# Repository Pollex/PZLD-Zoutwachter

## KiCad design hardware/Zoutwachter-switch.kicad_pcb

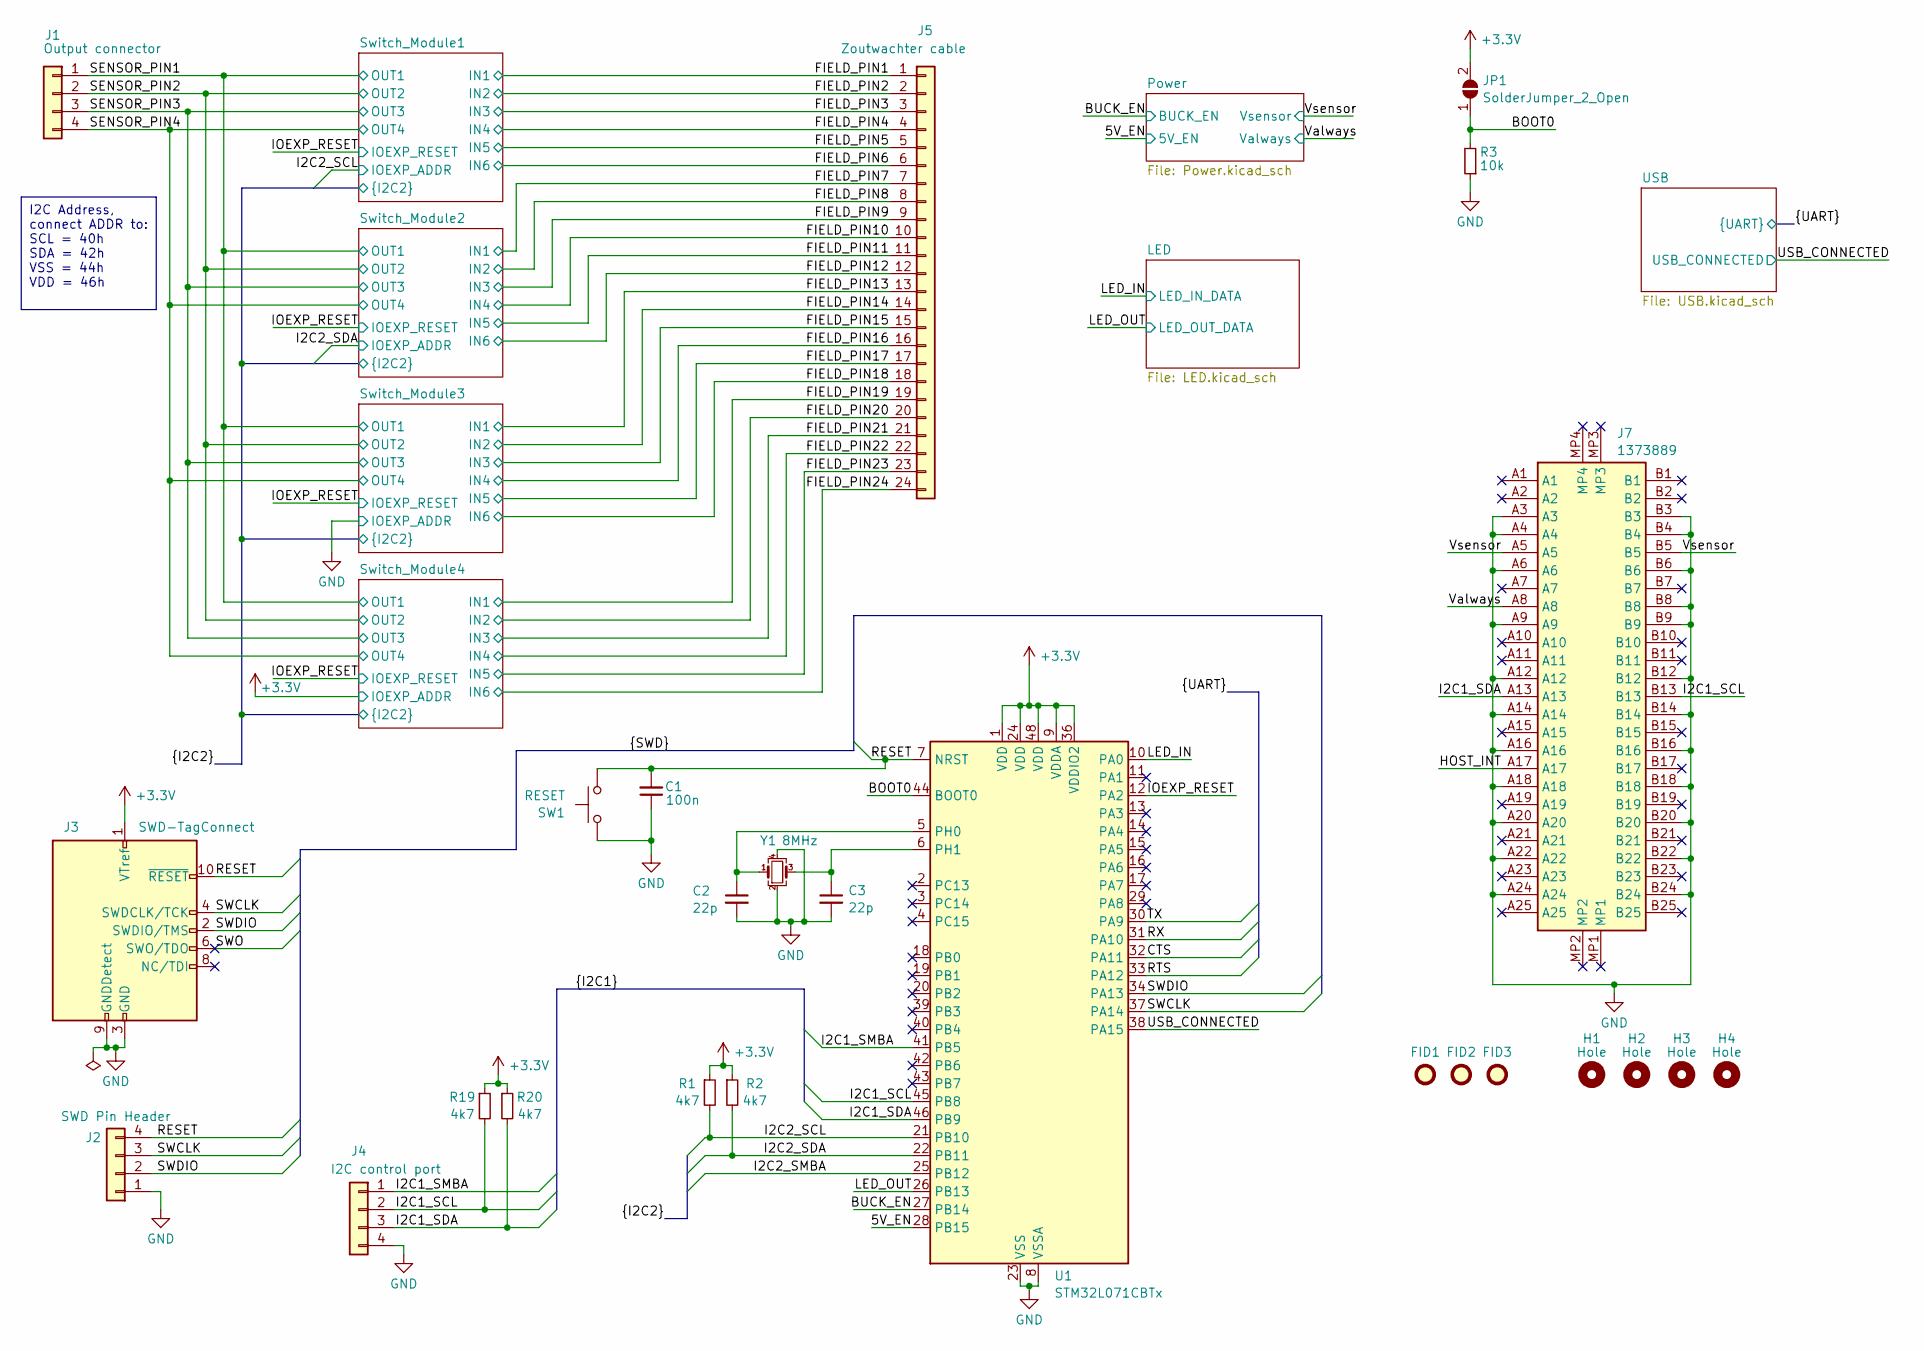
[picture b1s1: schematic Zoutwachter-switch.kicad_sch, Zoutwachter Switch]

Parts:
C1: 100n; C_0603_1608Metric; LCSC MFR YAGEO
C2, C3: 22p; C_0603_1608Metric; LCSC MFR Samsung Electro-Mechanics
FID1, FID2, FID3: Fiducial; Fiducial_1mm_Mask2mm
H1, H2, H3, H4: Hole; MountingHole_3.2mm_M3
J1: Output connector; 1755752
J2: SWD Pin Header; DEALON DW254S-22-04-85 SMD 2x2pin 2.54mm straight; LCSC MFR DEALON
J3: SWD-TagConnect; Tag-Connect_TC2050-IDC-NL_2x05_P1.27mm_Vertical_with_bottom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
J4: I2C control port; DEALON DW254S-22-04-85 SMD 2x2pin 2.54mm straight; LCSC MFR DEALON
J5: Zoutwachter cable; 1755956
J7: 1373889; Manufacturer_Part_Number 1373889
JP1: SolderJumper_2_Open; SolderJumper-2_P1.3mm_Open_RoundedPad1.0x1.5mm
R1, R2, R19, R20: 4k7; R_0603_1608Metric; LCSC MFR UNI-ROYAL(Uniroyal Elec)
R3: 10k; R_0603_1608Metric; LCSC MFR UNI-ROYAL(Uniroyal Elec)
SW1: RESET; SW_Push_1P1T_XKB_TS-1187A; LCSC MFR XKB Connectivity
U1: STM32L071CBTx; LQFP-48_7x7mm_P0.5mm; LCSC MFR STMicroelectronics
Y1: 8MHz; Crystal_SMD_3225-4Pin_3.2x2.5mm; LCSC MFR ECS INTERNATIONAL INC

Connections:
/5V_EN: U1.28 (PB15); also elsewhere on the board
/BOOT0: JP1.1 (A), R3.2, U1.44 (BOOT0)
/BUCK_EN: U1.27 (PB14); also elsewhere on the board
/CTS: U1.32 (PA11); also elsewhere on the board
/FIELD_PIN1: J5.1; also elsewhere on the board
/FIELD_PIN2: J5.2; also elsewhere on the board
/FIELD_PIN3: J5.3; also elsewhere on the board
/FIELD_PIN4: J5.4; also elsewhere on the board
/FIELD_PIN5: J5.5; also elsewhere on the board
/FIELD_PIN6: J5.6; also elsewhere on the board
/FIELD_PIN7: J5.7; also elsewhere on the board
/FIELD_PIN8: J5.8; also elsewhere on the board
/FIELD_PIN9: J5.9; also elsewhere on the board
/FIELD_PIN10: J5.10; also elsewhere on the board
/FIELD_PIN11: J5.11; also elsewhere on the board
/FIELD_PIN12: J5.12; also elsewhere on the board
/FIELD_PIN13: J5.13; also elsewhere on the board
/FIELD_PIN14: J5.14; also elsewhere on the board
/FIELD_PIN15: J5.15; also elsewhere on the board
/FIELD_PIN16: J5.16; also elsewhere on the board
/FIELD_PIN17: J5.17; also elsewhere on the board
/FIELD_PIN18: J5.18; also elsewhere on the board
/FIELD_PIN19: J5.19; also elsewhere on the board
/FIELD_PIN20: J5.20; also elsewhere on the board
/FIELD_PIN21: J5.21; also elsewhere on the board
/FIELD_PIN22: J5.22; also elsewhere on the board
/FIELD_PIN23: J5.23; also elsewhere on the board
/FIELD_PIN24: J5.24; also elsewhere on the board
/HOST_INT: J7.A17
/I2C1_SCL: J4.2, J7.B13, R19.2, U1.45 (PB8)
/I2C1_SDA: J4.3, J7.A13, R20.2, U1.46 (PB9)
/I2C1_SMBA: J4.1, U1.41 (PB5)
/I2C2_SCL: R1.2, U1.21 (PB10); also elsewhere on the board
/I2C2_SDA: R2.2, U1.22 (PB11); also elsewhere on the board
/I2C2_SMBA: U1.25 (PB12)
/IOEXP_RESET: U1.12 (PA2); also elsewhere on the board
/LED_IN: U1.10 (PA0); also elsewhere on the board
/LED_OUT: U1.26 (PB13); also elsewhere on the board
/RESET: C1.2, J2.4, J3.10 (~RESET), SW1.2, U1.7 (NRST)
/RTS: U1.33 (PA12); also elsewhere on the board
/RX: U1.31 (PA10); also elsewhere on the board
/SENSOR_PIN1: J1.1; also elsewhere on the board
/SENSOR_PIN2: J1.2; also elsewhere on the board
/SENSOR_PIN3: J1.3; also elsewhere on the board
/SENSOR_PIN4: J1.4; also elsewhere on the board
/SWCLK: J2.3, J3.4 (SWDCLK/TCK), U1.37 (PA14)
/SWDIO: J2.2, J3.2 (SWDIO/TMS), U1.34 (PA13)
/SWO: J3.6 (SWO/TDO)
/TX: U1.30 (PA9); also elsewhere on the board
/USB_CONNECTED: U1.38 (PA15); also elsewhere on the board
/Valways: J7.A8; also elsewhere on the board
/Vsensor: J7.A5, J7.B5; also elsewhere on the board
GND: C1.1, C2.2, C3.2, J2.1, J3.3 (GND), J3.5 (GND), J3.9 (GNDDetect), J4.4, J7.A3, J7.A4, J7.A6, J7.A9, J7.A12, J7.A14, J7.A16, J7.A18, J7.A20, J7.A22, J7.A24, J7.B3, J7.B4, J7.B6, J7.B8, J7.B9, J7.B12, J7.B14, J7.B16, J7.B18, J7.B20, J7.B22, J7.B24, R3.1, SW1.1, U1.8 (VSSA), U1.23 (VSS), U1.35 (VSS), U1.47 (VSS), Y1.2, Y1.4; also elsewhere on the board
unnamed: C2.1, U1.5 (PH0), Y1.1
unnamed: C3.1, U1.6 (PH1), Y1.3

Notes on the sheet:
I2C Address, connect ADDR to: ﻿SCL = 40h SDA = 42h VSS = 44h VDD = 46h

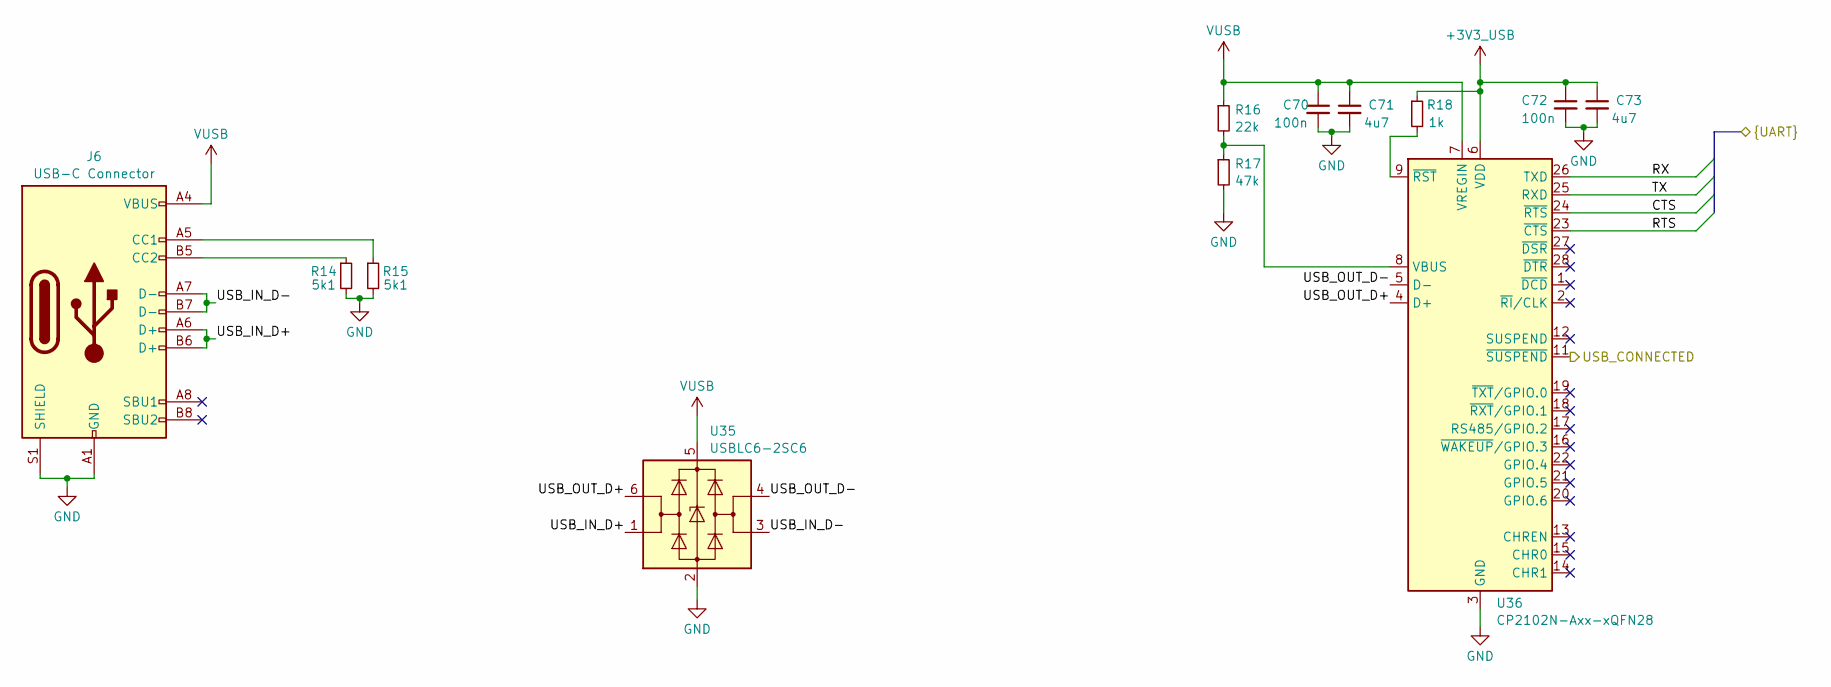
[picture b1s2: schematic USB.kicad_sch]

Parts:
C70, C72: 100n; C_0603_1608Metric; LCSC MFR YAGEO
C71, C73: 4u7; C_0603_1608Metric; LCSC MFR Samsung Electro-Mechanics
J6: USB-C Connector; MOLEX_2171820001; LCSC MFR MOLEX
R14, R15: 5k1; R_0603_1608Metric; LCSC MFR UNI-ROYAL(Uniroyal Elec)
R16: 22k; R_0603_1608Metric; LCSC MFR UNI-ROYAL(Uniroyal Elec)
R17: 47k; R_0603_1608Metric; LCSC MFR UNI-ROYAL(Uniroyal Elec)
R18: 1k; R_0603_1608Metric; LCSC MFR UNI-ROYAL(Uniroyal Elec)
U35: USBLC6-2SC6; SOT-23-6; LCSC MFR STMicroelectronics
U36: CP2102N-Axx-xQFN28; QFN-28-1EP_5x5mm_P0.5mm_EP3.35x3.35mm; LCSC MFR SILICON LABS

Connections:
+3V3_USB: C72.1, C73.1, R18.1, U36.6 (VDD)
/CTS: U36.24 (~RTS); also elsewhere on the board
/RTS: U36.23 (~CTS); also elsewhere on the board
/RX: U36.26 (TXD); also elsewhere on the board
/TX: U36.25 (RXD); also elsewhere on the board
/USB/USB_IN_D+: J6.A6 (D+), J6.B6 (D+), U35.1 (I/O1)
/USB/USB_IN_D-: J6.A7 (D-), J6.B7 (D-), U35.3 (I/O2)
/USB/USB_OUT_D+: U35.6 (I/O1), U36.4 (D+)
/USB/USB_OUT_D-: U35.4 (I/O2), U36.5 (D-)
/USB_CONNECTED: U36.11 (~SUSPEND); also elsewhere on the board
GND: C70.2, C71.2, C72.2, C73.2, J6.A1 (GND), J6.A12 (GND), J6.B1 (GND), J6.B12 (GND), J6.S1 (SHIELD), R14.2, R15.2, R17.2, U35.2 (GND), U36.3 (GND), U36.29 (GND); also elsewhere on the board
unnamed: J6.A5 (CC1), R15.1
unnamed: J6.B5 (CC2), R14.1
unnamed: R16.2, R17.1, U36.8 (VBUS)
unnamed: R18.2, U36.9 (~RST)
VUSB: C70.1, C71.1, J6.A4 (VBUS), J6.A9 (VBUS), J6.B4 (VBUS), J6.B9 (VBUS), R16.1, U35.5 (VBUS), U36.7 (VREGIN); also elsewhere on the board

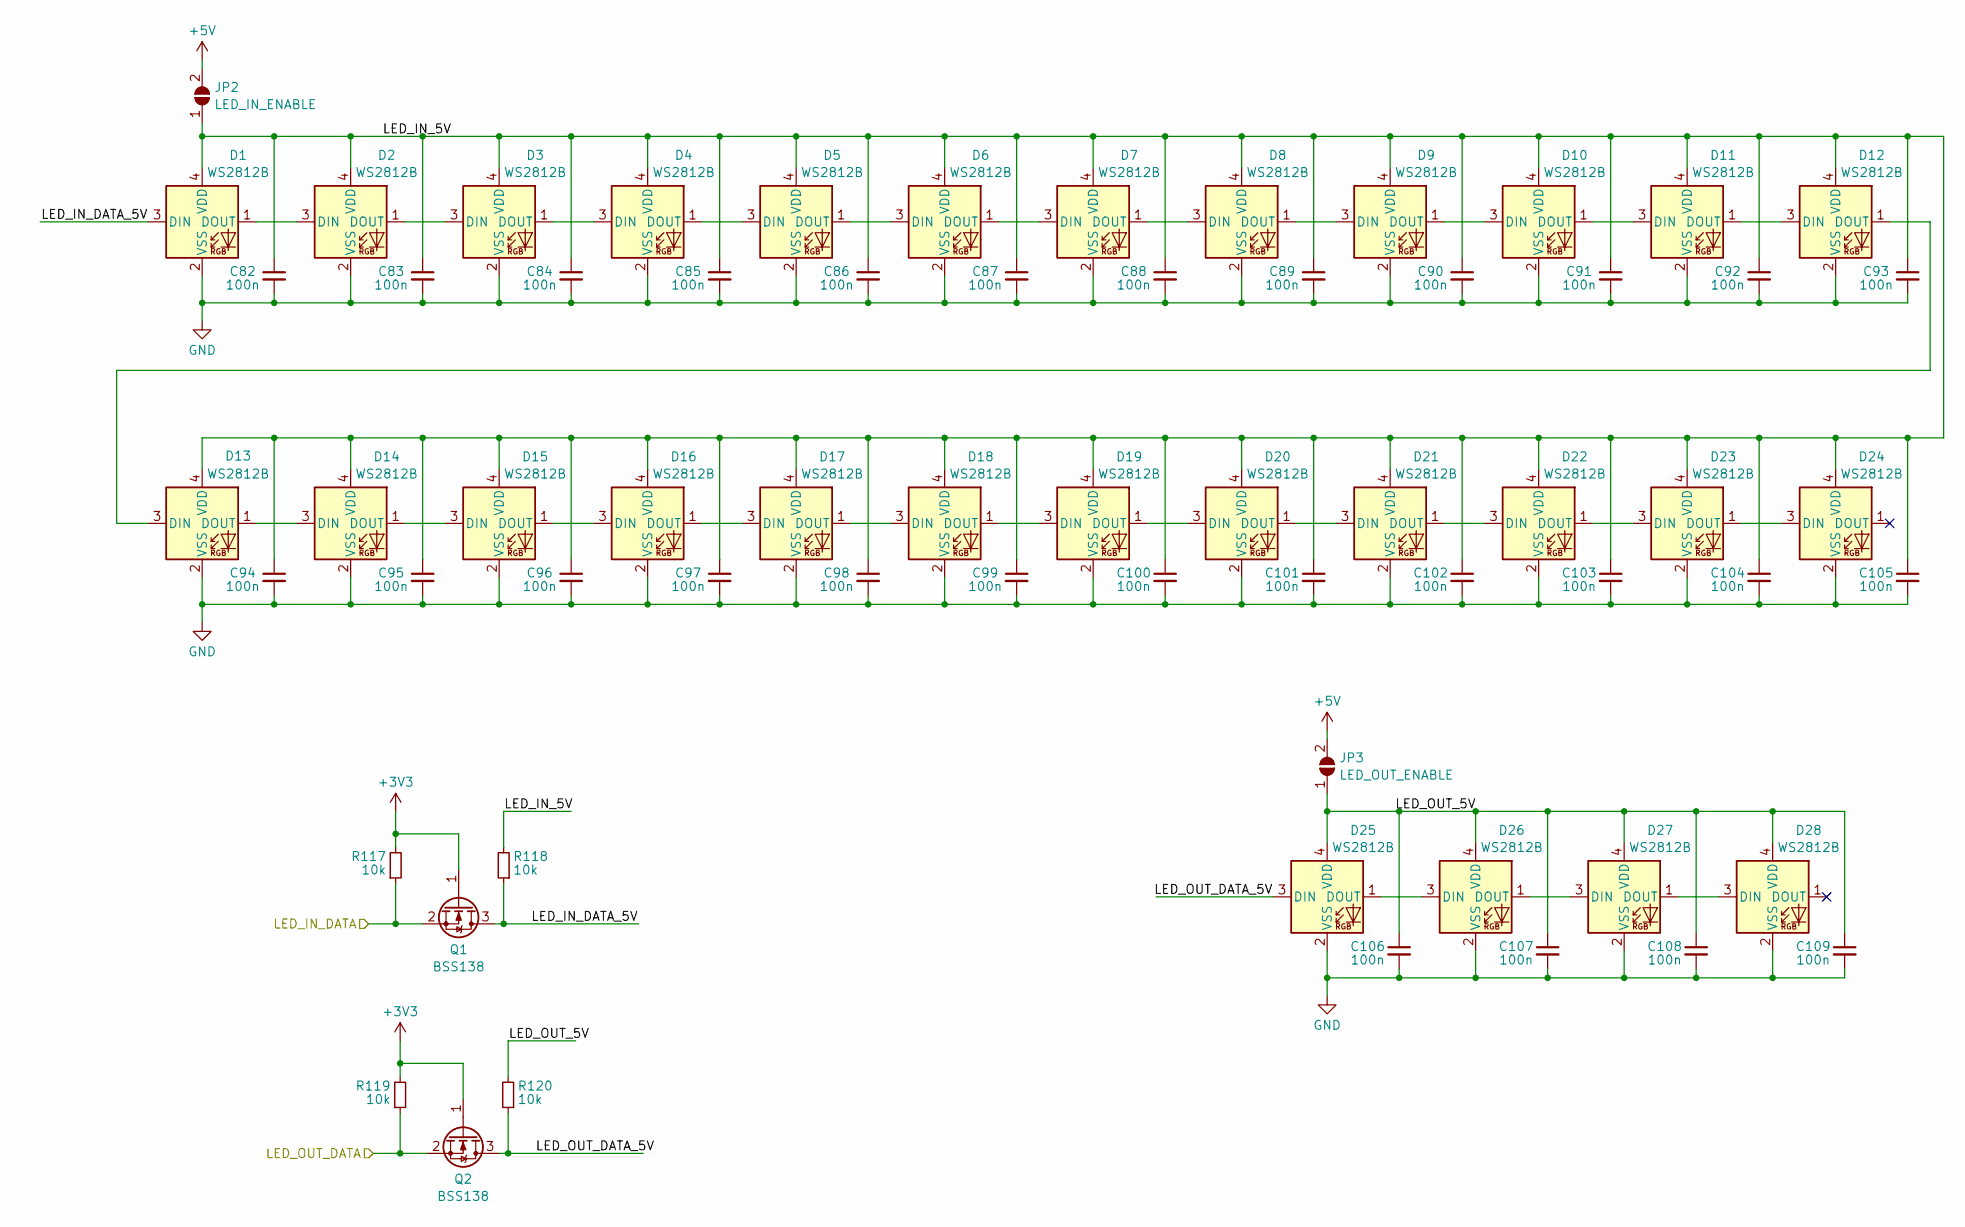
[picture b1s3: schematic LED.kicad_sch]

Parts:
C82, C83, C84, C85, C86, C87, C88, C89, C90, C91, C92, C93, C94, C95, C96, C97, C98, C99, C100, C101, C102, C103, C104, C105, C106, C107, C108, C109: 100n; C_0603_1608Metric; LCSC MFR YAGEO
D1, D2, D3, D4, D5, D6, D7, D8, D9, D10, D11, D12, D13, D14, D15, D16, D17, D18, D19, D20, D21, D22, D23, D24, D25, D26, D27, D28: WS2812B; WS2812B-2020; LCSC MFR Worldsemi
JP2: LED_IN_ENABLE; SolderJumper-2_P1.3mm_Open_RoundedPad1.0x1.5mm
JP3: LED_OUT_ENABLE; SolderJumper-2_P1.3mm_Open_RoundedPad1.0x1.5mm
Q1, Q2: BSS138; SOT-23
R117, R118, R119, R120: 10k; R_0603_1608Metric; LCSC MFR UNI-ROYAL(Uniroyal Elec)

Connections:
+5V: JP2.2 (B), JP3.2 (B); also elsewhere on the board
/LED/LED_IN_5V: C82.1, C83.1, C84.1, C85.1, C86.1, C87.1, C88.1, C89.1, C90.1, C91.1, C92.1, C93.1, C94.1, C95.1, C96.1, C97.1, C98.1, C99.1, C100.1, C101.1, C102.1, C103.1, C104.1, C105.1, D1.4 (VDD), D2.4 (VDD), D3.4 (VDD), D4.4 (VDD), D5.4 (VDD), D6.4 (VDD), D7.4 (VDD), D8.4 (VDD), D9.4 (VDD), D10.4 (VDD), D11.4 (VDD), D12.4 (VDD), D13.4 (VDD), D14.4 (VDD), D15.4 (VDD), D16.4 (VDD), D17.4 (VDD), D18.4 (VDD), D19.4 (VDD), D20.4 (VDD), D21.4 (VDD), D22.4 (VDD), D23.4 (VDD), D24.4 (VDD), JP2.1 (A), R118.2
/LED/LED_IN_DATA_5V: D1.3 (DIN), Q1.3 (D), R118.1
/LED/LED_OUT_5V: C106.1, C107.1, C108.1, C109.1, D25.4 (VDD), D26.4 (VDD), D27.4 (VDD), D28.4 (VDD), JP3.1 (A), R120.2
/LED/LED_OUT_DATA_5V: D25.3 (DIN), Q2.3 (D), R120.1
/LED_IN: Q1.2 (S), R117.1; also elsewhere on the board
/LED_OUT: Q2.2 (S), R119.1; also elsewhere on the board
GND: C82.2, C83.2, C84.2, C85.2, C86.2, C87.2, C88.2, C89.2, C90.2, C91.2, C92.2, C93.2, C94.2, C95.2, C96.2, C97.2, C98.2, C99.2, C100.2, C101.2, C102.2, C103.2, C104.2, C105.2, C106.2, C107.2, C108.2, C109.2, D1.2 (VSS), D2.2 (VSS), D3.2 (VSS), D4.2 (VSS), D5.2 (VSS), D6.2 (VSS), D7.2 (VSS), D8.2 (VSS), D9.2 (VSS), D10.2 (VSS), D11.2 (VSS), D12.2 (VSS), D13.2 (VSS), D14.2 (VSS), D15.2 (VSS), D16.2 (VSS), D17.2 (VSS), D18.2 (VSS), D19.2 (VSS), D20.2 (VSS), D21.2 (VSS), D22.2 (VSS), D23.2 (VSS), D24.2 (VSS), D25.2 (VSS), D26.2 (VSS), D27.2 (VSS), D28.2 (VSS); also elsewhere on the board
unnamed: D1.1 (DOUT), D2.3 (DIN)
unnamed: D2.1 (DOUT), D3.3 (DIN)
unnamed: D3.1 (DOUT), D4.3 (DIN)
unnamed: D4.1 (DOUT), D5.3 (DIN)
unnamed: D5.1 (DOUT), D6.3 (DIN)
unnamed: D6.1 (DOUT), D7.3 (DIN)
unnamed: D7.1 (DOUT), D8.3 (DIN)
unnamed: D8.1 (DOUT), D9.3 (DIN)
unnamed: D9.1 (DOUT), D10.3 (DIN)
unnamed: D10.1 (DOUT), D11.3 (DIN)
unnamed: D11.1 (DOUT), D12.3 (DIN)
unnamed: D12.1 (DOUT), D13.3 (DIN)
unnamed: D13.1 (DOUT), D14.3 (DIN)
unnamed: D14.1 (DOUT), D15.3 (DIN)
unnamed: D15.1 (DOUT), D16.3 (DIN)
unnamed: D16.1 (DOUT), D17.3 (DIN)
unnamed: D17.1 (DOUT), D18.3 (DIN)
unnamed: D18.1 (DOUT), D19.3 (DIN)
unnamed: D19.1 (DOUT), D20.3 (DIN)
unnamed: D20.1 (DOUT), D21.3 (DIN)
unnamed: D21.1 (DOUT), D22.3 (DIN)
unnamed: D22.1 (DOUT), D23.3 (DIN)
unnamed: D23.1 (DOUT), D24.3 (DIN)
unnamed: D25.1 (DOUT), D26.3 (DIN)
unnamed: D26.1 (DOUT), D27.3 (DIN)
unnamed: D27.1 (DOUT), D28.3 (DIN)

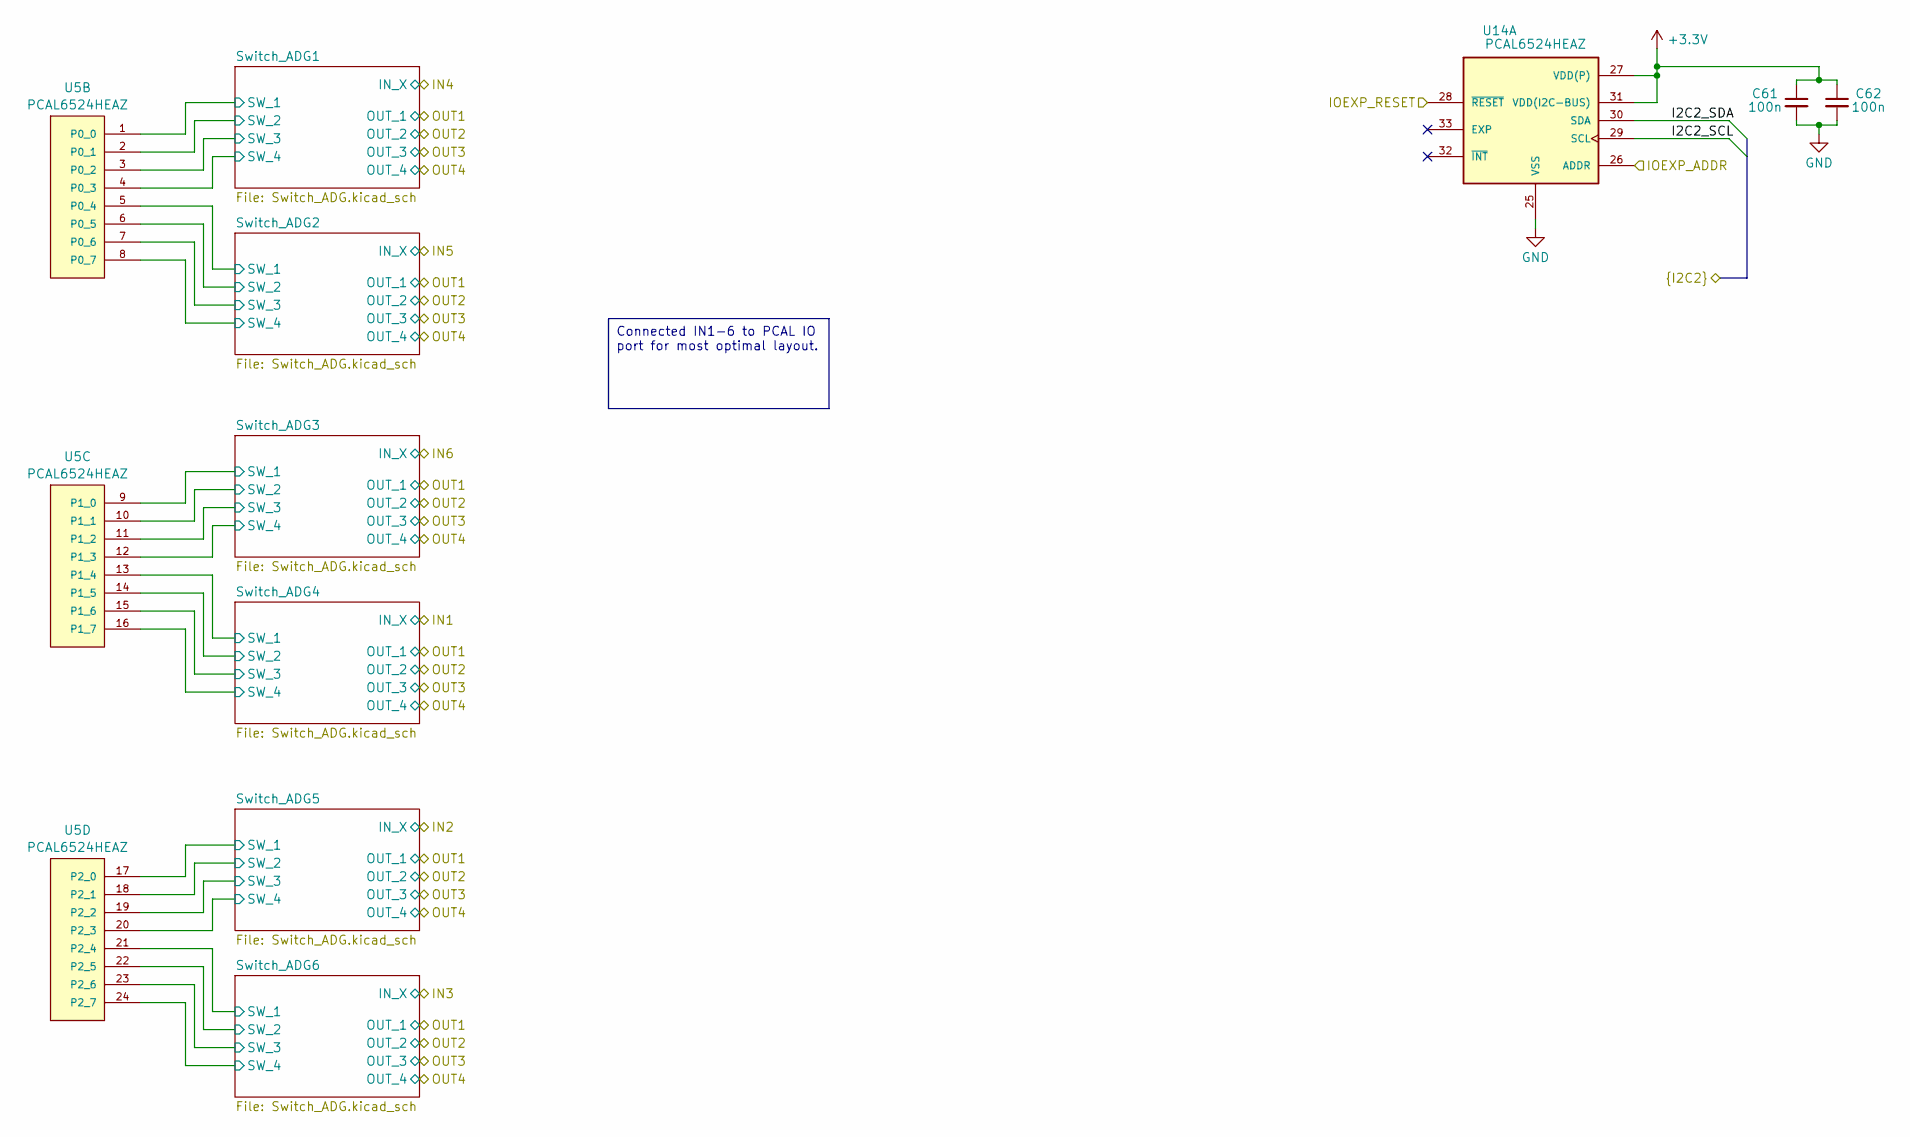
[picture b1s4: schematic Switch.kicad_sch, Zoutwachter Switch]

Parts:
C61, C62: 100n; C_0603_1608Metric; LCSC MFR YAGEO
U5, U14: PCAL6524HEAZ; LCSC Part # C3000497

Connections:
/I2C2_SCL: U5.26 (ADDR), U5.29 (SCL), U14.29 (SCL); also elsewhere on the board
/I2C2_SDA: U5.30 (SDA), U14.30 (SDA); also elsewhere on the board
/IOEXP_RESET: U5.28 (~RESET), U14.28 (~RESET); also elsewhere on the board
/Switch_Module1/Switch_ADG1/SW_1: U5.1 (P0_0); also elsewhere on the board
/Switch_Module1/Switch_ADG1/SW_2: U5.2 (P0_1); also elsewhere on the board
/Switch_Module1/Switch_ADG1/SW_3: U5.3 (P0_2); also elsewhere on the board
/Switch_Module1/Switch_ADG1/SW_4: U5.4 (P0_3); also elsewhere on the board
/Switch_Module1/Switch_ADG2/SW_1: U5.5 (P0_4); also elsewhere on the board
/Switch_Module1/Switch_ADG2/SW_2: U5.6 (P0_5); also elsewhere on the board
/Switch_Module1/Switch_ADG2/SW_3: U5.7 (P0_6); also elsewhere on the board
/Switch_Module1/Switch_ADG2/SW_4: U5.8 (P0_7); also elsewhere on the board
/Switch_Module1/Switch_ADG3/SW_1: U5.9 (P1_0); also elsewhere on the board
/Switch_Module1/Switch_ADG3/SW_2: U5.10 (P1_1); also elsewhere on the board
/Switch_Module1/Switch_ADG3/SW_3: U5.11 (P1_2); also elsewhere on the board
/Switch_Module1/Switch_ADG3/SW_4: U5.12 (P1_3); also elsewhere on the board
/Switch_Module1/Switch_ADG4/SW_1: U5.13 (P1_4); also elsewhere on the board
/Switch_Module1/Switch_ADG4/SW_2: U5.14 (P1_5); also elsewhere on the board
/Switch_Module1/Switch_ADG4/SW_3: U5.15 (P1_6); also elsewhere on the board
/Switch_Module1/Switch_ADG4/SW_4: U5.16 (P1_7); also elsewhere on the board
/Switch_Module1/Switch_ADG5/SW_1: U5.17 (P2_0); also elsewhere on the board
/Switch_Module1/Switch_ADG5/SW_2: U5.18 (P2_1); also elsewhere on the board
/Switch_Module1/Switch_ADG5/SW_3: U5.19 (P2_2); also elsewhere on the board
/Switch_Module1/Switch_ADG5/SW_4: U5.20 (P2_3); also elsewhere on the board
/Switch_Module1/Switch_ADG6/SW_1: U5.21 (P2_4); also elsewhere on the board
/Switch_Module1/Switch_ADG6/SW_2: U5.22 (P2_5); also elsewhere on the board
/Switch_Module1/Switch_ADG6/SW_3: U5.23 (P2_6); also elsewhere on the board
/Switch_Module1/Switch_ADG6/SW_4: U5.24 (P2_7); also elsewhere on the board
/Switch_Module4/Switch_ADG1/SW_1: U14.1 (P0_0); also elsewhere on the board
/Switch_Module4/Switch_ADG1/SW_2: U14.2 (P0_1); also elsewhere on the board
/Switch_Module4/Switch_ADG1/SW_3: U14.3 (P0_2); also elsewhere on the board
/Switch_Module4/Switch_ADG1/SW_4: U14.4 (P0_3); also elsewhere on the board
/Switch_Module4/Switch_ADG2/SW_1: U14.5 (P0_4); also elsewhere on the board
/Switch_Module4/Switch_ADG2/SW_2: U14.6 (P0_5); also elsewhere on the board
/Switch_Module4/Switch_ADG2/SW_3: U14.7 (P0_6); also elsewhere on the board
/Switch_Module4/Switch_ADG2/SW_4: U14.8 (P0_7); also elsewhere on the board
/Switch_Module4/Switch_ADG3/SW_1: U14.9 (P1_0); also elsewhere on the board
/Switch_Module4/Switch_ADG3/SW_2: U14.10 (P1_1); also elsewhere on the board
/Switch_Module4/Switch_ADG3/SW_3: U14.11 (P1_2); also elsewhere on the board
/Switch_Module4/Switch_ADG3/SW_4: U14.12 (P1_3); also elsewhere on the board
/Switch_Module4/Switch_ADG4/SW_1: U14.13 (P1_4); also elsewhere on the board
/Switch_Module4/Switch_ADG4/SW_2: U14.14 (P1_5); also elsewhere on the board
/Switch_Module4/Switch_ADG4/SW_3: U14.15 (P1_6); also elsewhere on the board
/Switch_Module4/Switch_ADG4/SW_4: U14.16 (P1_7); also elsewhere on the board
/Switch_Module4/Switch_ADG5/SW_1: U14.17 (P2_0); also elsewhere on the board
/Switch_Module4/Switch_ADG5/SW_2: U14.18 (P2_1); also elsewhere on the board
/Switch_Module4/Switch_ADG5/SW_3: U14.19 (P2_2); also elsewhere on the board
/Switch_Module4/Switch_ADG5/SW_4: U14.20 (P2_3); also elsewhere on the board
/Switch_Module4/Switch_ADG6/SW_1: U14.21 (P2_4); also elsewhere on the board
/Switch_Module4/Switch_ADG6/SW_2: U14.22 (P2_5); also elsewhere on the board
/Switch_Module4/Switch_ADG6/SW_3: U14.23 (P2_6); also elsewhere on the board
/Switch_Module4/Switch_ADG6/SW_4: U14.24 (P2_7); also elsewhere on the board
GND: C61.2, C62.2, U5.25 (VSS), U14.25 (VSS); also elsewhere on the board

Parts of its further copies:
C19, C20, C33, C34, C47, C48: 100n; C_0603_1608Metric; LCSC MFR YAGEO
U12, U13: PCAL6524HEAZ; LCSC Part # C3000497

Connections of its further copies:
/I2C2_SCL: U12.29 (SCL), U13.29 (SCL); also elsewhere on the board
/I2C2_SDA: U12.26 (ADDR), U12.30 (SDA), U13.30 (SDA); also elsewhere on the board
/IOEXP_RESET: U12.28 (~RESET), U13.28 (~RESET); also elsewhere on the board
/Switch_Module2/Switch_ADG1/SW_1: U12.1 (P0_0); also elsewhere on the board
/Switch_Module2/Switch_ADG1/SW_2: U12.2 (P0_1); also elsewhere on the board
/Switch_Module2/Switch_ADG1/SW_3: U12.3 (P0_2); also elsewhere on the board
/Switch_Module2/Switch_ADG1/SW_4: U12.4 (P0_3); also elsewhere on the board
/Switch_Module2/Switch_ADG2/SW_1: U12.5 (P0_4); also elsewhere on the board
/Switch_Module2/Switch_ADG2/SW_2: U12.6 (P0_5); also elsewhere on the board
/Switch_Module2/Switch_ADG2/SW_3: U12.7 (P0_6); also elsewhere on the board
/Switch_Module2/Switch_ADG2/SW_4: U12.8 (P0_7); also elsewhere on the board
/Switch_Module2/Switch_ADG3/SW_1: U12.9 (P1_0); also elsewhere on the board
/Switch_Module2/Switch_ADG3/SW_2: U12.10 (P1_1); also elsewhere on the board
/Switch_Module2/Switch_ADG3/SW_3: U12.11 (P1_2); also elsewhere on the board
/Switch_Module2/Switch_ADG3/SW_4: U12.12 (P1_3); also elsewhere on the board
/Switch_Module2/Switch_ADG4/SW_1: U12.13 (P1_4); also elsewhere on the board
/Switch_Module2/Switch_ADG4/SW_2: U12.14 (P1_5); also elsewhere on the board
/Switch_Module2/Switch_ADG4/SW_3: U12.15 (P1_6); also elsewhere on the board
/Switch_Module2/Switch_ADG4/SW_4: U12.16 (P1_7); also elsewhere on the board
/Switch_Module2/Switch_ADG5/SW_1: U12.17 (P2_0); also elsewhere on the board
/Switch_Module2/Switch_ADG5/SW_2: U12.18 (P2_1); also elsewhere on the board
/Switch_Module2/Switch_ADG5/SW_3: U12.19 (P2_2); also elsewhere on the board
/Switch_Module2/Switch_ADG5/SW_4: U12.20 (P2_3); also elsewhere on the board
/Switch_Module2/Switch_ADG6/SW_1: U12.21 (P2_4); also elsewhere on the board
/Switch_Module2/Switch_ADG6/SW_2: U12.22 (P2_5); also elsewhere on the board
/Switch_Module2/Switch_ADG6/SW_3: U12.23 (P2_6); also elsewhere on the board
/Switch_Module2/Switch_ADG6/SW_4: U12.24 (P2_7); also elsewhere on the board
/Switch_Module3/Switch_ADG1/SW_1: U13.1 (P0_0); also elsewhere on the board
/Switch_Module3/Switch_ADG1/SW_2: U13.2 (P0_1); also elsewhere on the board
/Switch_Module3/Switch_ADG1/SW_3: U13.3 (P0_2); also elsewhere on the board
/Switch_Module3/Switch_ADG1/SW_4: U13.4 (P0_3); also elsewhere on the board
/Switch_Module3/Switch_ADG2/SW_1: U13.5 (P0_4); also elsewhere on the board
/Switch_Module3/Switch_ADG2/SW_2: U13.6 (P0_5); also elsewhere on the board
/Switch_Module3/Switch_ADG2/SW_3: U13.7 (P0_6); also elsewhere on the board
/Switch_Module3/Switch_ADG2/SW_4: U13.8 (P0_7); also elsewhere on the board
/Switch_Module3/Switch_ADG3/SW_1: U13.9 (P1_0); also elsewhere on the board
/Switch_Module3/Switch_ADG3/SW_2: U13.10 (P1_1); also elsewhere on the board
/Switch_Module3/Switch_ADG3/SW_3: U13.11 (P1_2); also elsewhere on the board
/Switch_Module3/Switch_ADG3/SW_4: U13.12 (P1_3); also elsewhere on the board
/Switch_Module3/Switch_ADG4/SW_1: U13.13 (P1_4); also elsewhere on the board
/Switch_Module3/Switch_ADG4/SW_2: U13.14 (P1_5); also elsewhere on the board
/Switch_Module3/Switch_ADG4/SW_3: U13.15 (P1_6); also elsewhere on the board
/Switch_Module3/Switch_ADG4/SW_4: U13.16 (P1_7); also elsewhere on the board
/Switch_Module3/Switch_ADG5/SW_1: U13.17 (P2_0); also elsewhere on the board
/Switch_Module3/Switch_ADG5/SW_2: U13.18 (P2_1); also elsewhere on the board
/Switch_Module3/Switch_ADG5/SW_3: U13.19 (P2_2); also elsewhere on the board
/Switch_Module3/Switch_ADG5/SW_4: U13.20 (P2_3); also elsewhere on the board
/Switch_Module3/Switch_ADG6/SW_1: U13.21 (P2_4); also elsewhere on the board
/Switch_Module3/Switch_ADG6/SW_2: U13.22 (P2_5); also elsewhere on the board
/Switch_Module3/Switch_ADG6/SW_3: U13.23 (P2_6); also elsewhere on the board
/Switch_Module3/Switch_ADG6/SW_4: U13.24 (P2_7); also elsewhere on the board
GND: C19.2, C20.2, C33.2, C34.2, C47.2, C48.2, U12.25 (VSS), U13.25 (VSS), U13.26 (ADDR); also elsewhere on the board

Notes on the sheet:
Connected IN1-6 to PCAL IO port for most optimal layout.

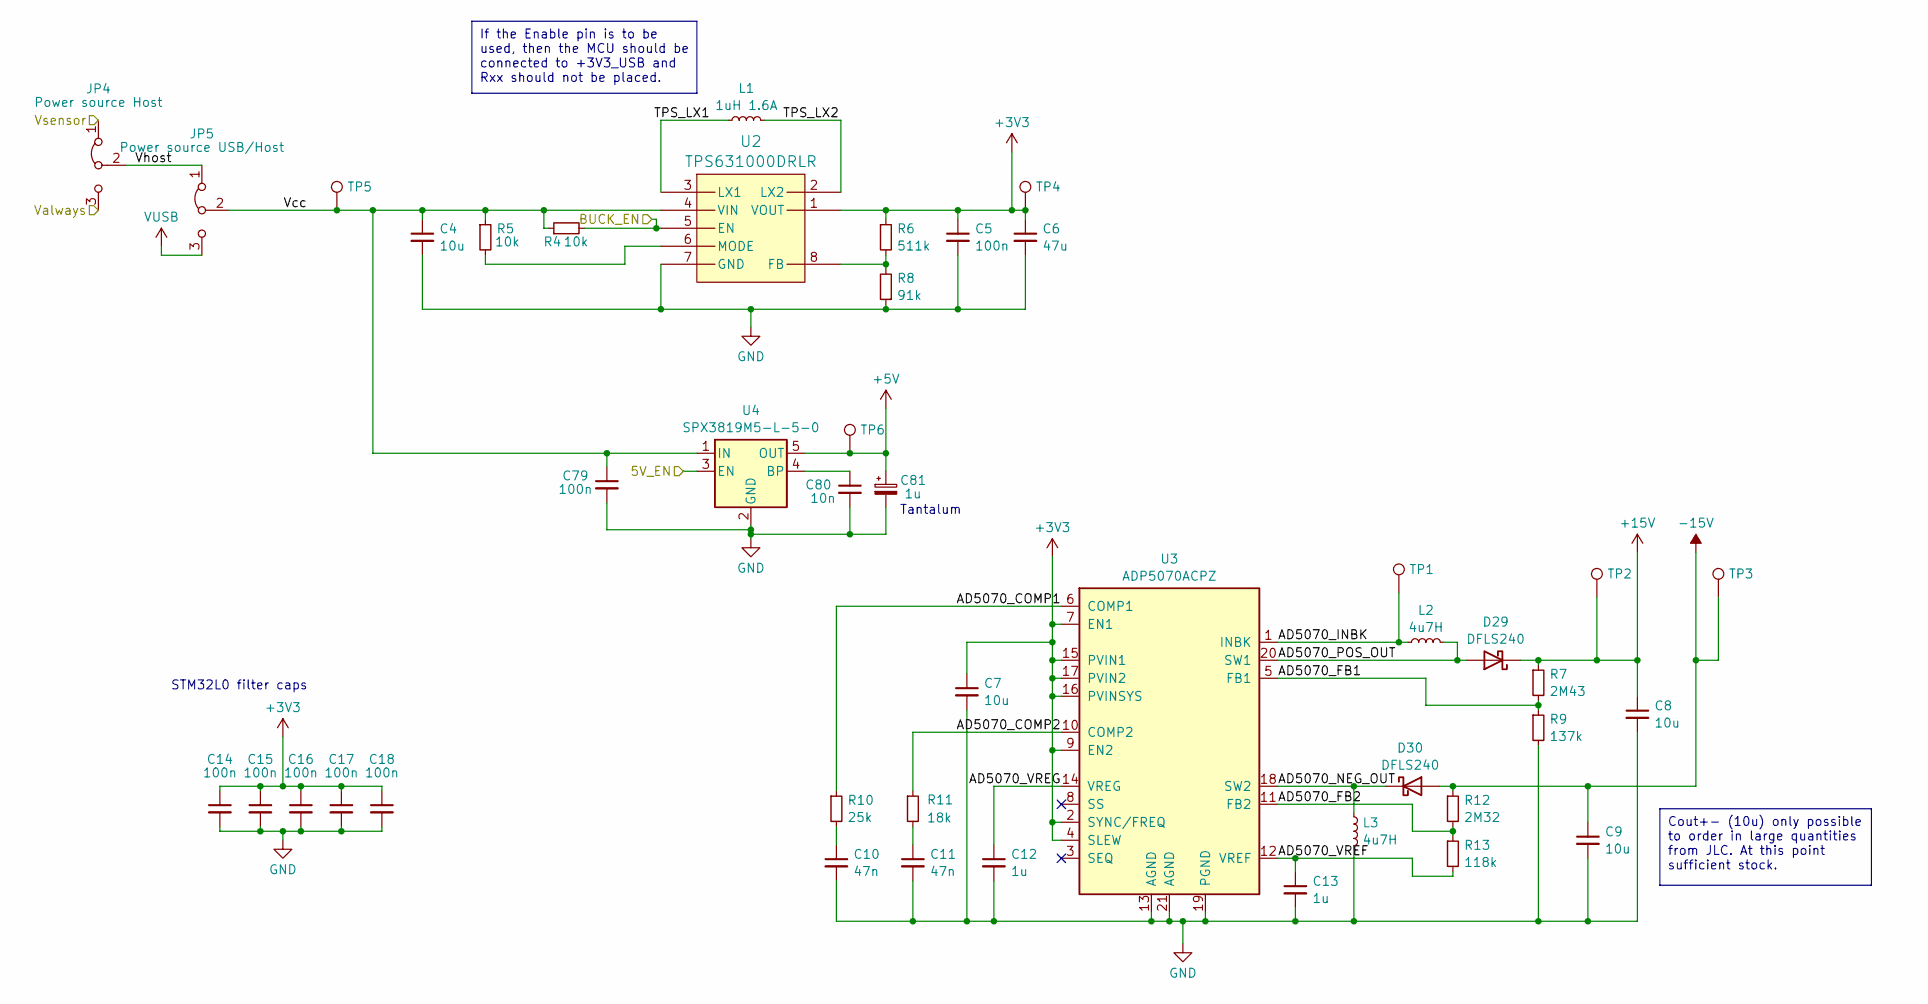
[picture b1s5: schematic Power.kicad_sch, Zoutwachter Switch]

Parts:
C4, C7: 10u; C_1206_3216Metric; LCSC MFR Taiyo Yuden
C5, C14, C15, C16, C17, C18, C79: 100n; C_0603_1608Metric; LCSC MFR YAGEO
C6: 47u; C_0603_1608Metric; LCSC MFR Samsung Electro-Mechanics
C8, C9: 10u; C_1210_3225Metric; LCSC MFR Murata Electronics
C10, C11: 47n; C_0603_1608Metric; LCSC MFR Murata Electronics
C12, C13: 1u; C_0603_1608Metric; LCSC MFR Murata Electronics
C80: 10n; C_0603_1608Metric; LCSC MFR FH (Guangdong Fenghua Advanced Tech)
C81: 1u; CP_EIA-1608-08_AVX-J; LCSC MFR Vishay Intertech
D29, D30: DFLS240; D_PowerDI-123; LCSC MFR Diodes Inc.
JP4: Power source Host; PinHeader_1x03_P2.54mm_Vertical
JP5: Power source USB/Host; PinHeader_1x03_P2.54mm_Vertical
L1: 1uH 1.6A; L_0603_1608Metric; LCSC MFR Murata Electronics
L2, L3: 4u7H; L_Wuerth_MAPI-4030; LCSC MFR WURTH ELEKTRONIK
R4, R5: 10k; R_0603_1608Metric; LCSC MFR UNI-ROYAL(Uniroyal Elec)
R6: 511k; R_0603_1608Metric; LCSC MFR YAGEO
R7: 2M43; R_0603_1608Metric; LCSC MFR YAGEO
R8: 91k; R_0603_1608Metric; LCSC MFR YAGEO
R9: 137k; R_0603_1608Metric; LCSC MFR YAGEO
R10: 25k; R_0603_1608Metric; LCSC MFR Viking Tech
R11: 18k; R_0603_1608Metric; LCSC MFR UNI-ROYAL(Uniroyal Elec)
R12: 2M32; R_0603_1608Metric; LCSC MFR YAGEO
R13: 118k; R_0603_1608Metric; LCSC MFR YAGEO
TP1, TP2, TP3, TP4, TP5, TP6: TestPoint_Pad_D1.5mm
U2: TPS631000DRLR; TPS631000DRLR_TEX; LCSC MFR TEXAS INSTRUMENTS
U3: ADP5070ACPZ; LFCSP-20-1EP_4x4mm_P0.5mm_EP2.6x2.6mm; LCSC Part # C659268
U4: SPX3819M5-L-5-0; SOT-23-5

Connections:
+5V: C81.1, TP6.1, U4.5 (OUT); also elsewhere on the board
+15V: C8.1, D29.1 (K), R7.1, TP2.1; also elsewhere on the board
-15V: C9.1, D30.2 (A), R12.1, TP3.1; also elsewhere on the board
/5V_EN: U4.3 (EN); also elsewhere on the board
/BUCK_EN: R4.2, U2.5 (EN); also elsewhere on the board
/Power/AD5070_COMP1: R10.1, U3.6 (COMP1)
/Power/AD5070_COMP2: R11.1, U3.10 (COMP2)
/Power/AD5070_FB1: R7.2, R9.1, U3.5 (FB1)
/Power/AD5070_FB2: R12.2, R13.1, U3.11 (FB2)
/Power/AD5070_INBK: L2.1, TP1.1, U3.1 (INBK)
/Power/AD5070_NEG_OUT: D30.1 (K), L3.1, U3.18 (SW2)
/Power/AD5070_POS_OUT: D29.2 (A), L2.2, U3.20 (SW1)
/Power/AD5070_VREF: C13.1, R13.2, U3.12 (VREF)
/Power/AD5070_VREG: C12.1, U3.14 (VREG)
/Power/TPS_LX1: L1.1, U2.3 (LX1)
/Power/TPS_LX2: L1.2, U2.2 (LX2)
/Power/Vcc: C4.1, C79.1, JP5.2 (C), R4.1, R5.1, TP5.1, U2.4 (VIN), U4.1 (IN)
/Power/Vhost: JP4.2 (C), JP5.1 (A)
/Valways: JP4.3 (B); also elsewhere on the board
/Vsensor: JP4.1 (A); also elsewhere on the board
GND: C4.2, C5.2, C6.2, C7.2, C8.2, C9.2, C10.2, C11.2, C12.2, C13.2, C14.2, C15.2, C16.2, C17.2, C18.2, C79.2, C80.2, C81.2, L3.2, R8.1, R9.2, U2.7 (GND), U3.13 (AGND), U3.19 (PGND), U3.21 (AGND), U4.2 (GND); also elsewhere on the board
unnamed: C10.1, R10.2
unnamed: C11.1, R11.2
unnamed: R6.2, R8.2, U2.8 (FB)
unnamed: R5.2, U2.6 (MODE)
unnamed: C80.1, U4.4 (BP)
VUSB: JP5.3 (B); also elsewhere on the board

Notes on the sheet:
Cout+- (10u) only possible to order in large quantities from JLC. At this point sufficient stock.
If the Enable pin is to be used, then the MCU should be connected to +3V3_USB and Rxx should not be placed.
STM32L0 filter caps
Tantalum
